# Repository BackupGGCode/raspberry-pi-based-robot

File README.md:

# RaspberryPi-based robot
Raspberry Pi based robot that can be controlled via an Android phone or a PC WiFi. The robot returns the on-board camera image so remote control can be realized.

(A large part of this repository is written in Hungarian, I would sugger you to use Google Translate or Reverso)

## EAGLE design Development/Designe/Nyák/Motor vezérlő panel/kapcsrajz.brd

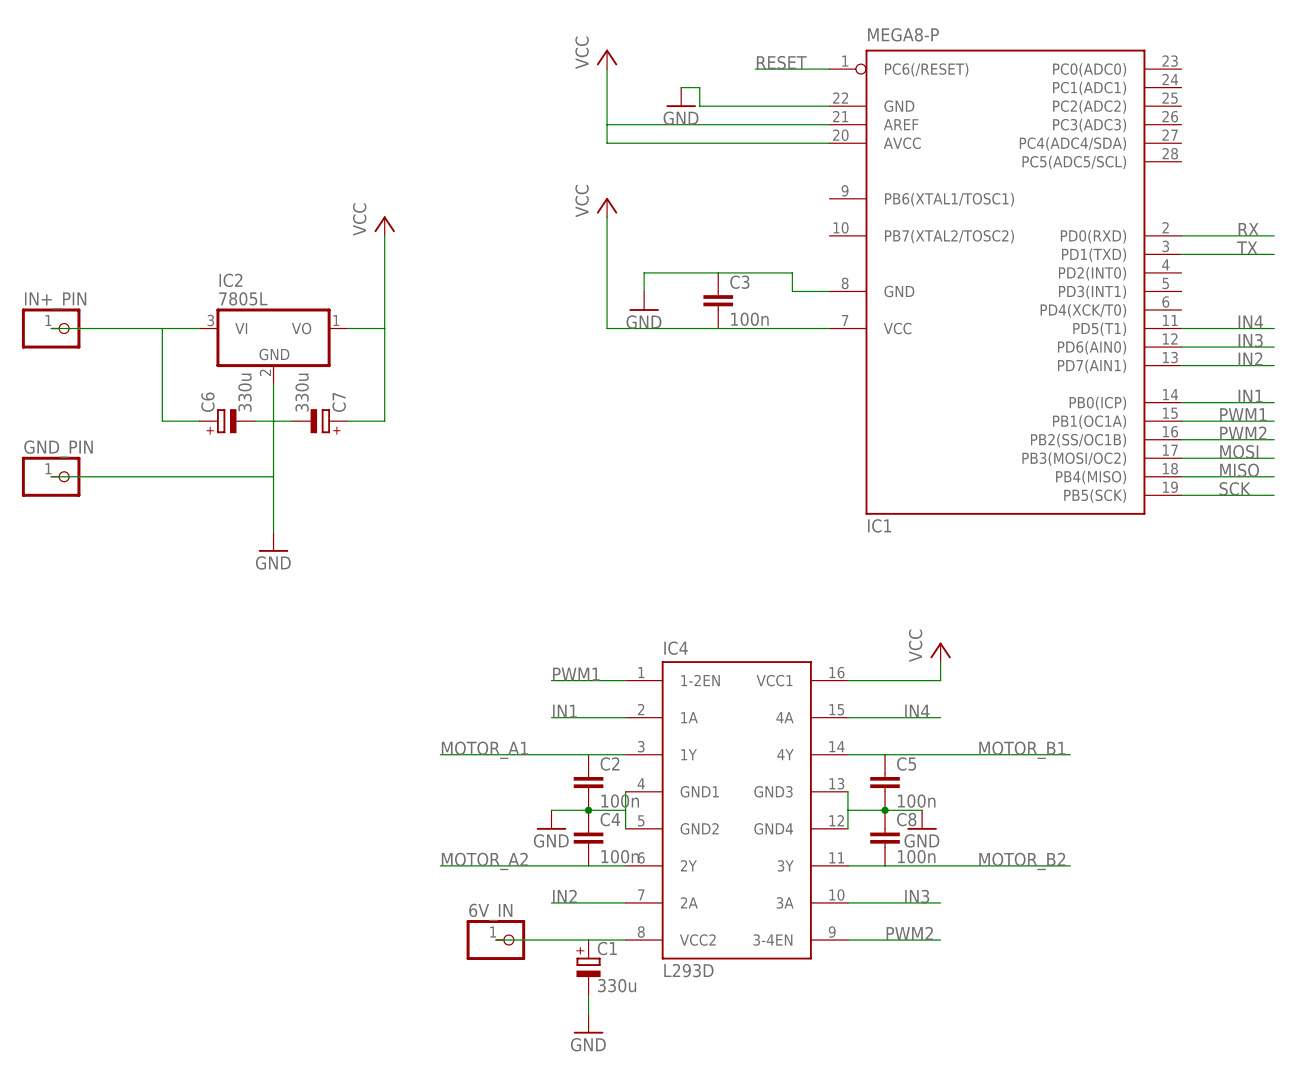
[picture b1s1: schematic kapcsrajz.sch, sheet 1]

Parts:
6V_IN: PINHD-1X1; 1X01
C1, C6, C7: 330u; E2,5-6E
C2, C3, C4, C5, C8: 100n; C025-030X050
GND_PIN: PINHD-1X1; 1X01
IC1: MEGA8-P; DIL28-3
IC2: 7805L; TO92
IC4: L293D; DIL16
IN+_PIN: PINHD-1X1; 1X01

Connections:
GND: C1.-, C2.2, C3.1, C4.1, C5.2, C6.-, C7.-, C8.1, GND_PIN.1, IC1.8 (GND), IC1.22 (GND), IC2.2 (GND), IC4.4 (GND1), IC4.5 (GND2), IC4.12 (GND4), IC4.13 (GND3); also elsewhere on the board
IN1: IC1.14 (PB0(ICP)), IC4.2 (1A)
IN2: IC1.13 (PD7(AIN1)), IC4.7 (2A)
IN3: IC1.12 (PD6(AIN0)), IC4.10 (3A)
IN4: IC1.11 (PD5(T1)), IC4.15 (4A)
MISO: IC1.18 (PB4(MISO)); also elsewhere on the board
MOSI: IC1.17 (PB3(MOSI/OC2)); also elsewhere on the board
MOTOR_A1: C2.1, IC4.3 (1Y); also elsewhere on the board
MOTOR_A2: C4.2, IC4.6 (2Y); also elsewhere on the board
MOTOR_B1: C5.1, IC4.14 (4Y); also elsewhere on the board
MOTOR_B2: C8.2, IC4.11 (3Y); also elsewhere on the board
unnamed: C6.+, IC2.3 (VI), IN+_PIN.1
unnamed: 6V_IN.1, C1.+, IC4.8 (VCC2)
PWM1: IC1.15 (PB1(OC1A)), IC4.1 (1-2EN)
PWM2: IC1.16 (PB2(SS/OC1B)), IC4.9 (3-4EN)
RESET: IC1.1 (PC6(/RESET)); also elsewhere on the board
RX: IC1.2 (PD0(RXD)); also elsewhere on the board
SCK: IC1.19 (PB5(SCK)); also elsewhere on the board
TX: IC1.3 (PD1(TXD)); also elsewhere on the board
VCC: C3.2, C7.+, IC1.7 (VCC), IC1.20 (AVCC), IC1.21 (AREF), IC2.1 (VO), IC4.16 (VCC1); also elsewhere on the board

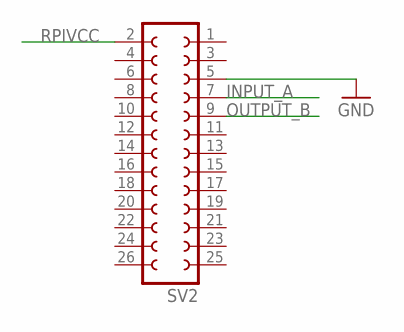
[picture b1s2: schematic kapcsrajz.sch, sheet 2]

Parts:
SV2: FE13-2

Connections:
GND: SV2.5; also elsewhere on the board
INPUT_A: SV2.7; also elsewhere on the board
OUTPUT_B: SV2.9; also elsewhere on the board
RPIVCC: SV2.2; also elsewhere on the board

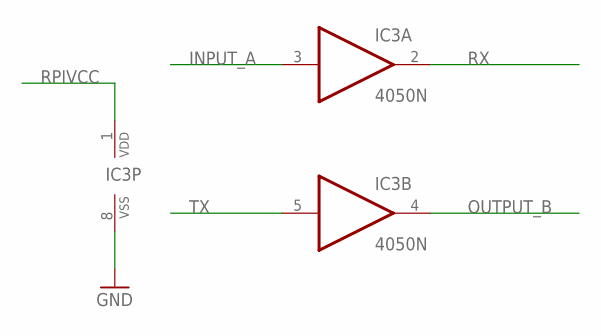
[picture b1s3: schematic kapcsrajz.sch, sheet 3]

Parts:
IC3: 4050N; DIL16

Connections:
GND: IC3.8 (VSS); also elsewhere on the board
INPUT_A: IC3.3 (I); also elsewhere on the board
OUTPUT_B: IC3.4 (O); also elsewhere on the board
RPIVCC: IC3.1 (VDD); also elsewhere on the board
RX: IC3.2 (O); also elsewhere on the board
TX: IC3.5 (I); also elsewhere on the board

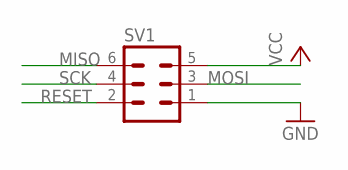
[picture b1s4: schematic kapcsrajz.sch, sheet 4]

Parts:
SV1: MA03-2

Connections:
GND: SV1.1; also elsewhere on the board
MISO: SV1.6; also elsewhere on the board
MOSI: SV1.3; also elsewhere on the board
RESET: SV1.2; also elsewhere on the board
SCK: SV1.4; also elsewhere on the board
VCC: SV1.5; also elsewhere on the board

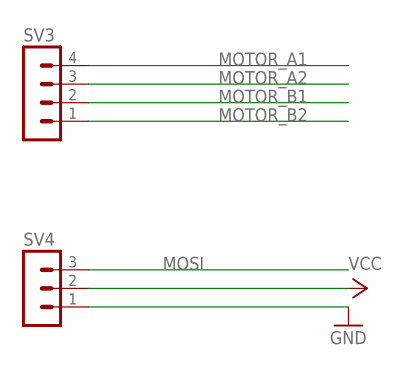
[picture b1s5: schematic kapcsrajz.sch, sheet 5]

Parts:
SV3: MA04-1
SV4: MA03-1

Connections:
GND: SV4.1; also elsewhere on the board
MOSI: SV4.3; also elsewhere on the board
MOTOR_A1: SV3.4; also elsewhere on the board
MOTOR_A2: SV3.3; also elsewhere on the board
MOTOR_B1: SV3.2; also elsewhere on the board
MOTOR_B2: SV3.1; also elsewhere on the board
VCC: SV4.2; also elsewhere on the board

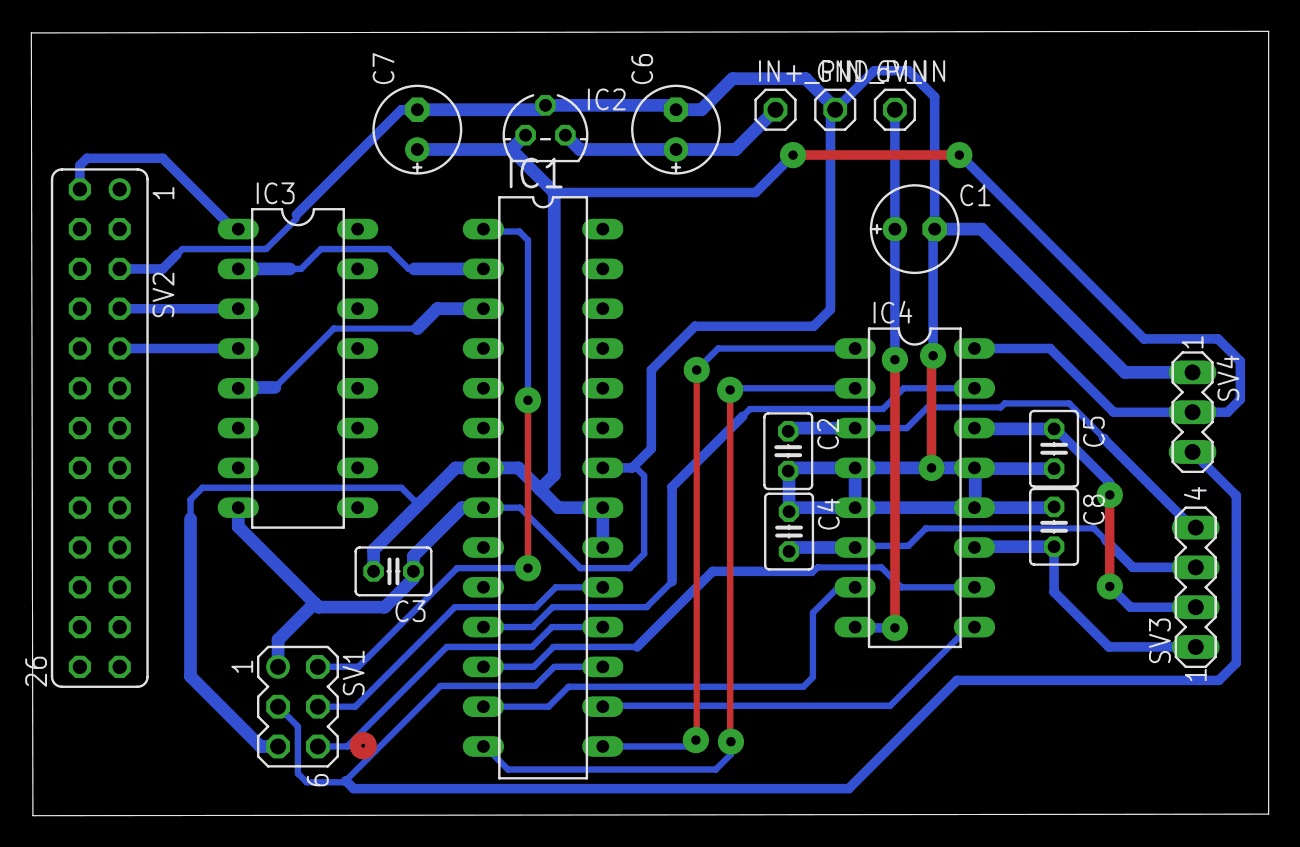
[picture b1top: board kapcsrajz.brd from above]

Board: 2 copper layers, 79.0 x 50.1 mm, 19 parts (0 on the bottom side), 23 nets.

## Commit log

2014-10-15 Ismerkedés a google code-al.
2014-10-16 Raspberry Pi felkészítése a robot vezérlő szoftver futtatására.
2014-10-16 Alaktrész sablonok.
2014-10-18 Meglévő kódok és nyáktervek.
2014-10-20 Algodoo szimulációk alternatív alvázhoz.
2014-10-20 Linkek nyáktervezéshez.
2014-10-21 Tartó panel.
2014-10-25 Anyag költségek
2014-10-25 MJPEG stream raspberry pi-ról.
2014-10-26 MPEG fogadás - jobb megoldás
2014-10-26 Mintaprogram, amely bemutatja, hogy egy Qt projektben, hogyan kell behúzni Opencv-t. A mintaprogram maga, csak bertölt egy képet egy előre megadott helyről. Forditásnál a kódban a kép elérési útvonal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
2014-10-26 átnevezés
2014-10-26 Megjegyzés
2014-10-26 mjpeg stream megnyitása,
2014-10-29 Működő kód, ami megnyitja az RPI-ről az mjpg streamet.
2014-10-29 Ezzel a megoldásal sikerült megcsinálni a webkamera stream küldését az RPI-ről a Qt-s kliens felé (illetve webes felületre) mjpg-ben.
2014-10-30 Ember detektor kód minta és paraméterek.
2014-10-30 Teljes képernyős megjelenítés Opencv-vel.
2014-10-31 Sima motorvezérlés és kommunikáció módosítása. Szervó motor vezérlés beépítése.
2014-11-04 Egyszerű arcdetektor.
2014-11-04 imshow kirakás teljes képernyőre.
2014-11-08 - Sketch Code könyvtár átnvezése Sketch_Code -ra, mert a Qt nem szereti a szóközt a projekt elérési útvonalában. - Imshow nélküli mejelenítés cv::Mat -> QImage-be történő konvertálásával.
2014-11-09 Alternatív kommunikáció
2014-11-09 Célkereszt
2014-11-10 imshow nélüli megjelenítés.
2014-11-11 Kivétel kezelés
2014-11-11 Kivétel kezelés bekötése. throw_line()-al lehet mostmár kivételeket dobni. TODO: A kivételek tartalmát új, felugró ablakban kellene megjeleníteni.
2014-11-16 Objektum detektálás kiszervezése külön szálra.
2014-11-17 Futtatás szünetre rakása
2014-11-26 Kommentkben ötletek
2015-02-02 Wall-e designe
2015-04-29 Rename költségek.txt to requirements.txt
